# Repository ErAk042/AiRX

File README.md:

# AiRX
AiRX is a modularized fully-analog superheterodyne AM radio receiver for the aviation band (117-140MHz). The system consists of an input filter + LNA, a LNA + mixer stege for converting the band to 7-30MHz range, a Xtal oscillator at 110MHz as the first LO, and a LA1267 based AM radio to demodulate the signal with an additional LM386 amp for driving speakers.

.png)

## Input Stage
The input stage is a 9th order bandpass filter (117-40MHz passband) made using high-q aircore inductors. Right after the filter, there is a LNA block made using the BFP196W RF transistor. Bias network is made using a BC807 PNP transistor. The circuit aims to provide a 15mA current flow over the RF transistor. The overall gain of the LNA block here is around 15dB. The final PCB ins enclosed in a phosphorus-bronze enclosure and the power supply cable is filtered by going through a ferride bead to minimize the RF interference by nearby electronics.

The input stage inside it's enclosure. The sides of the lid are bent frequently with small cuts to improve the seal.

The populated PCB of the input stage. The 3rd SMA connector on the long edge was a temporary test point between the filter and LNA.

## 110MHz Oscillator
A 22MHz crystal is used in 5th overtone to achieve 110MHz 1st LO frequency. There is a filter at the output of the oscillator buffer to filter out any potential harmonics/noise.

## Mixer Stage
The mixer used to bring the band down to the HF range is a SA612 double balanced mixer. At the RF input there is another LNA based on the same BFP196W transistor. It's the same circuit as the input stage LNA, only difference being that the current going through the transistor is roughly 1.4x higher. After that, the signal is fed to the 612's RF input with a 4:1 balun. Since the input impedance of the 612 is around 2kOhms, this balun allows the output of the transistor to be matched better than a straight transmission line. Since the band used is pretty wide, a matching network was not a practical solution in this case.
The 110MHz is directly fed into the base of the internal oscillator transistor of the 612.
At the output, there is a LPF with a cutoff frequency of 30MHz. This both filters out the images and reduces the overall noise level of the system.

The back side of the mixer module.

The front side of the mixer module.

## AM Demodulator
The signals from the mixer module is directly fed to the input of this module. This is a superheterodyne shortwave radio based on the LA1267 chip by Sanyo. At the input, there is a variable band selective filter. The variable capacitor determines the band, as well as the LO frequency of the radio. The audio output is then fed into a LM386 amplifier. The outout can be directly used to drive medium-sized speakers. For the sake of conveniency, I later used a Si5351 frequency sythesizer controlled by an Arduino as the LO to precisely select the band that I wanted to listen to. I was able to account for the slight offset(24KHz) of the 110MHz oscillator with this solution, while achieving precise frequency control. This was a huge improvement since the bandwith is limited to 6-8KHz, which makes it hard to manually adjust the frequency using the variable capacitor without any pulley system. 

The back side of the demodulator module.

The front side of the demodulator module.

## Planned future updates
I'm palnning on using a variable frequency filter for the input stage, which shoould help with the overall sensetivity of the system by limiting the witdh of the band admitted. Also, I want to use a more powerful mixer for the fisr mixer stage, so the dynamic range of the system can be improved. An AGC system is also within my plans.

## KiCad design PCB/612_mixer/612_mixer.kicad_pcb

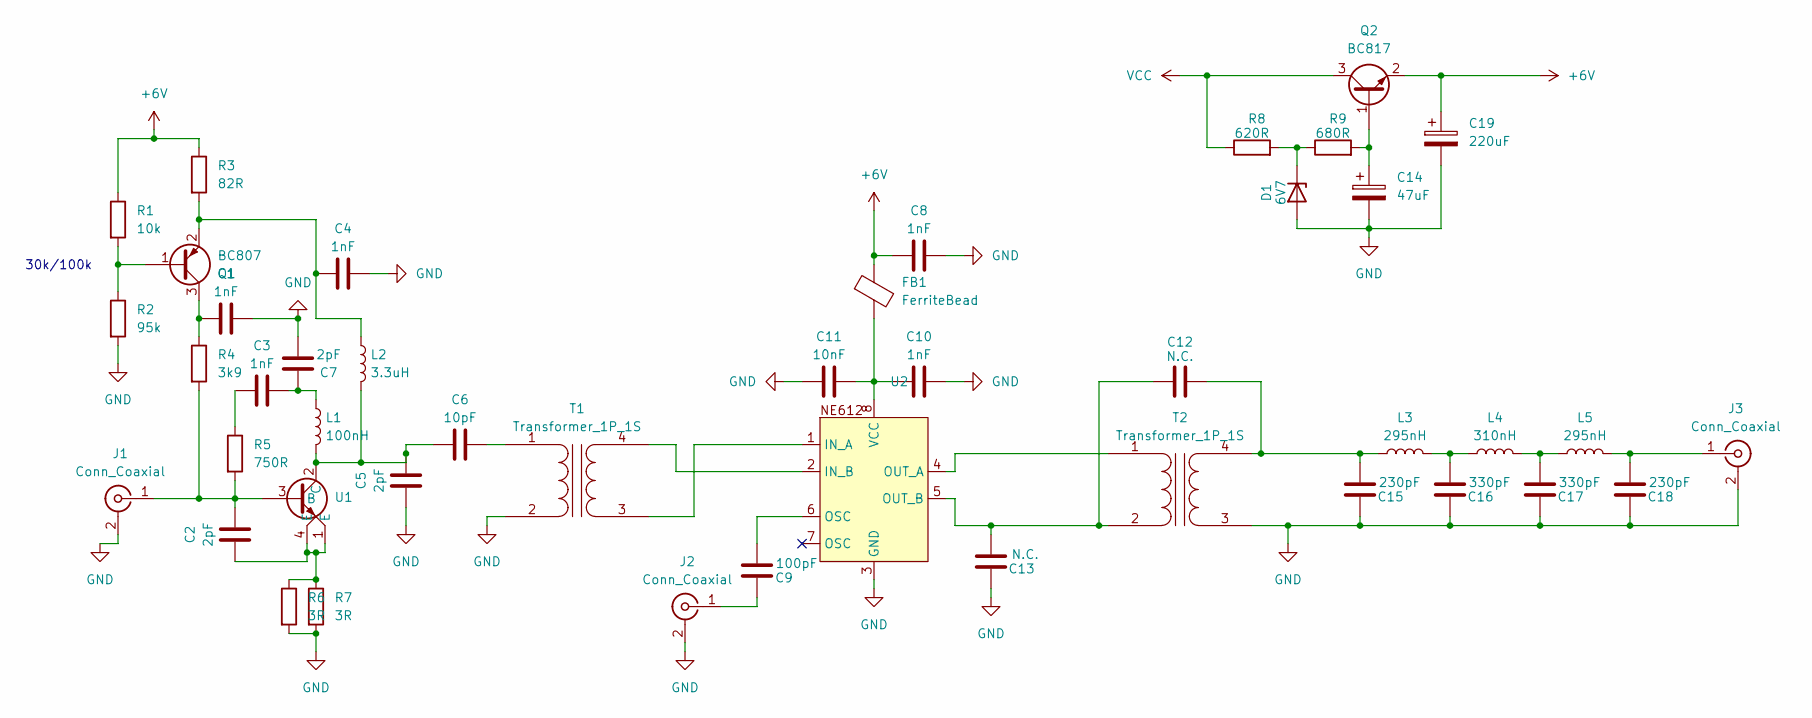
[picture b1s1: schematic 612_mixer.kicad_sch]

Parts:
C1, C3, C4, C8, C10: 1nF; C_0603_1608Metric
C2, C5, C7: 2pF; C_0603_1608Metric
C6: 10pF; C_0603_1608Metric
C9: 100pF; C_0603_1608Metric
C11: 10nF; C_0603_1608Metric
C12, C13: N.C.; C_0603_1608Metric
C14: 47uF; CP_EIA-3528-21_Kemet-B
C15, C18: 230pF; C_0603_1608Metric
C16, C17: 330pF; C_0603_1608Metric
C19: 220uF; CP_EIA-6032-28_Kemet-C
D1: 6V7; L_1206_3216Metric
FB1: FerriteBead; C_0603_1608Metric
J1, J2, J3: Conn_Coaxial; SMA_Samtec_SMA-J-P-H-ST-EM1_EdgeMount
L1: 100nH; L_0402_1005Metric
L2: 3.3uH; L_1008_2520Metric
L3, L5: 295nH; R_Axial_DIN0207_L6.3mm_D2.5mm_P7.62mm_Horizontal
L4: 310nH; R_Axial_DIN0207_L6.3mm_D2.5mm_P7.62mm_Horizontal
Q1: BC807; SOT-323_SC-70
Q2: BC817; SOT-23
R1: 10k; R_0603_1608Metric
R2: 95k; R_0603_1608Metric
R3: 82R; R_0603_1608Metric
R4: 3k9; R_0603_1608Metric
R5: 750R; R_0603_1608Metric
R6, R7: 3R; R_0603_1608Metric
R8: 620R; R_0603_1608Metric
R9: 680R; R_0603_1608Metric
T1, T2: Transformer_1P_1S; SW_DIP_SPSTx02_Slide_6.7x6.64mm_W7.62mm_P2.54mm_LowProfile
U1: SOT343_Transistor
U2: DIP-8_W7.62mm

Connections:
+6V: C8.2, C19.1, FB1.1, Q2.2 (E), R1.1, R3.1
GND: C1.1, C4.1, C5.2, C7.2, C8.1, C10.1, C11.1, C13.1, C14.2, C15.1, C16.1, C17.1, C18.1, C19.2, D1.2 (A), J1.2 (Ext), J2.2 (Ext), J3.2 (Ext), R2.2, R6.2, R7.2, T1.2 (AB), T2.3 (SA), U2.3 (GND)
unnamed: C2.2, R6.1, R7.1, U1.1 (E), U1.4 (E)
unnamed: C3.1, C7.1, L1.1
unnamed: C3.2, R5.1
unnamed: C9.2, U2.6 (OSC)
unnamed: C16.2, L3.2, L4.1
unnamed: C17.2, L4.2, L5.1
unnamed: D1.1 (K), R8.2, R9.1
unnamed: C2.1, J1.1 (In), R4.2, R5.2, U1.3 (B)
unnamed: C9.1, J2.1 (In)
unnamed: C18.2, J3.1 (In), L5.2
unnamed: Q1.1 (B), R1.2, R2.1
unnamed: C1.2, Q1.3 (C), R4.1
unnamed: C4.2, L2.1, Q1.2 (E), R3.2
unnamed: C14.1, Q2.1 (B), R9.2
unnamed: C6.1, T1.1 (AA)
unnamed: T1.3 (SA), U2.1 (IN_A)
unnamed: T1.4 (SB), U2.2 (IN_B)
unnamed: T2.1 (AA), U2.4 (OUT_A)
unnamed: C12.2, C13.2, T2.2 (AB), U2.5 (OUT_B)
unnamed: C12.1, C15.2, L3.1, T2.4 (SB)
unnamed: C5.1, C6.2, L1.2, L2.2, U1.2 (C)
unnamed: C10.2, C11.2, FB1.2, U2.8 (VCC)
VCC: Q2.3 (C), R8.1

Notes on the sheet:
30k/100k

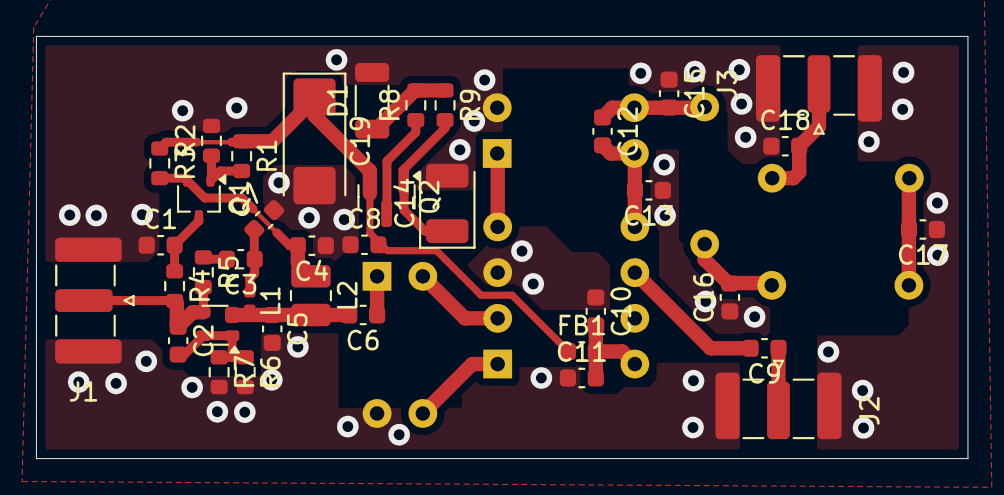
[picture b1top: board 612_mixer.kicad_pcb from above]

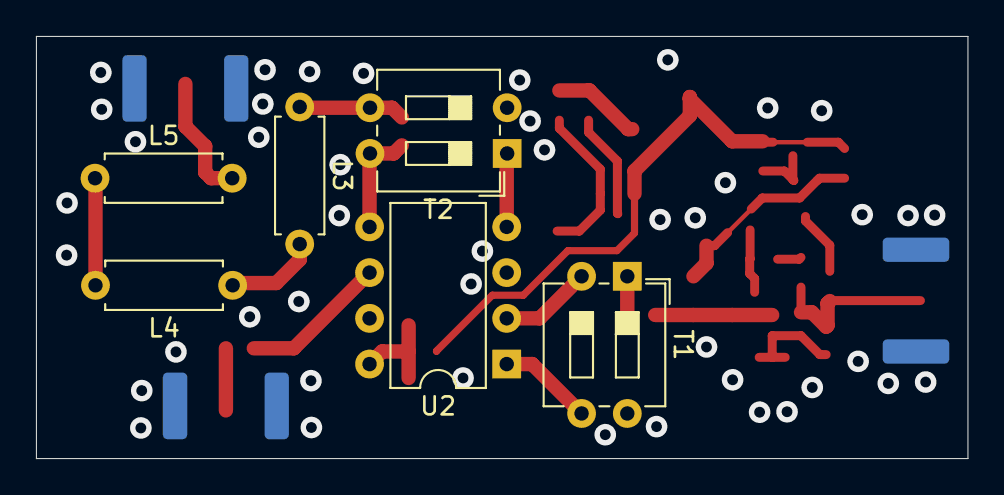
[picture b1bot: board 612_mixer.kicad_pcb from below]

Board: 2 copper layers, 51.8 x 23.5 mm, 44 parts (6 on the bottom side), 25 nets.

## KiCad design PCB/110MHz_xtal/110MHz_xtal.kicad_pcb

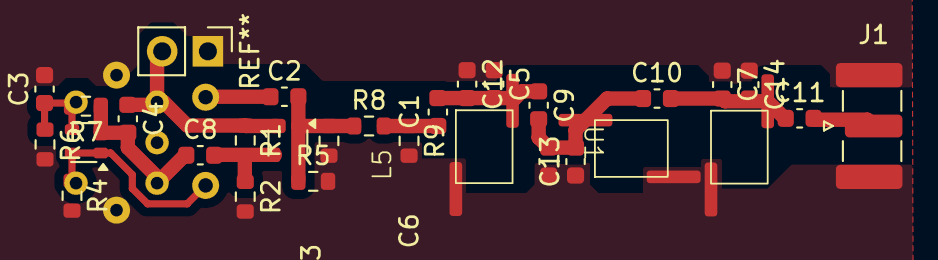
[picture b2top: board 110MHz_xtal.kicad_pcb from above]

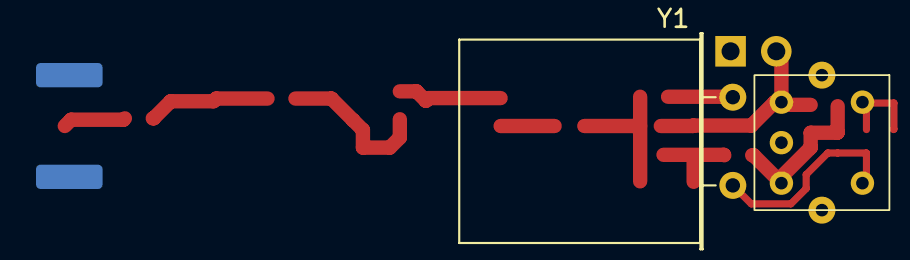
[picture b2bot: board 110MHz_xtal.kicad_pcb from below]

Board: 2 copper layers, 31 parts (2 on the bottom side), 13 nets.

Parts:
C1, C11: 2.9pF; C_0603_1608Metric
C2: 15pF; C_0603_1608Metric
C3, C4, C8: 1nF; C_0603_1608Metric
C5, C12: 17.67pF; C_0603_1608Metric
C6, C13: 20.12pF; C_0603_1608Metric
C7, C14: 17.62pF; C_0603_1608Metric
C9, C10: 0.5pF; C_0603_1608Metric
J1: Conn_Coaxial_Small; SMA_Samtec_SMA-J-P-H-ST-EM1_EdgeMount
L1: Inductor_IF
L4, L5, L6: L; inductor_small
R1: 51k; R_0603_1608Metric
R2, R6: N.C.; R_0603_1608Metric
R3, R8, R9: 15k; R_0603_1608Metric
R4: 330R; R_0603_1608Metric
R5: 150R; R_0603_1608Metric
R7: 470k; R_0603_1608Metric
U1, U2: SOT343_Transistor
Y1: Crystal; Crystal_HC49-U_Horizontal

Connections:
+BATT: C4.1, L1.1, R1.1, U1.2 (C)
GND: C3.2, C5.1, C6.1, C7.1, C12.1, C13.1, C14.1, J1.2 (Ext), L1.6, L4.1, L5.1, L6.1, R2.2, R3.2, R4.2, R5.2, R6.2, R9.2
unnamed: C1.1, R8.2, R9.1
unnamed: C1.2, C5.2, C9.1, C12.2, L4.2
unnamed: C2.1, Y1.1
unnamed: C2.2, R3.1, R5.1, R8.1, U1.1 (E), U1.4 (E)
unnamed: C6.2, C9.2, C10.1, C13.2, L5.2
unnamed: C7.2, C10.2, C11.1, C14.2, L6.2
unnamed: C11.2, J1.1 (In)
unnamed: L1.4, R4.1, U2.1 (E), U2.4 (E), Y1.2
unnamed: C8.2, R1.2, R2.1, U1.3 (B)
unnamed: C3.1, L1.5, R6.1, R7.2, U2.3 (B)
unnamed: C4.2, C8.1, L1.3, R7.1, U2.2 (C)

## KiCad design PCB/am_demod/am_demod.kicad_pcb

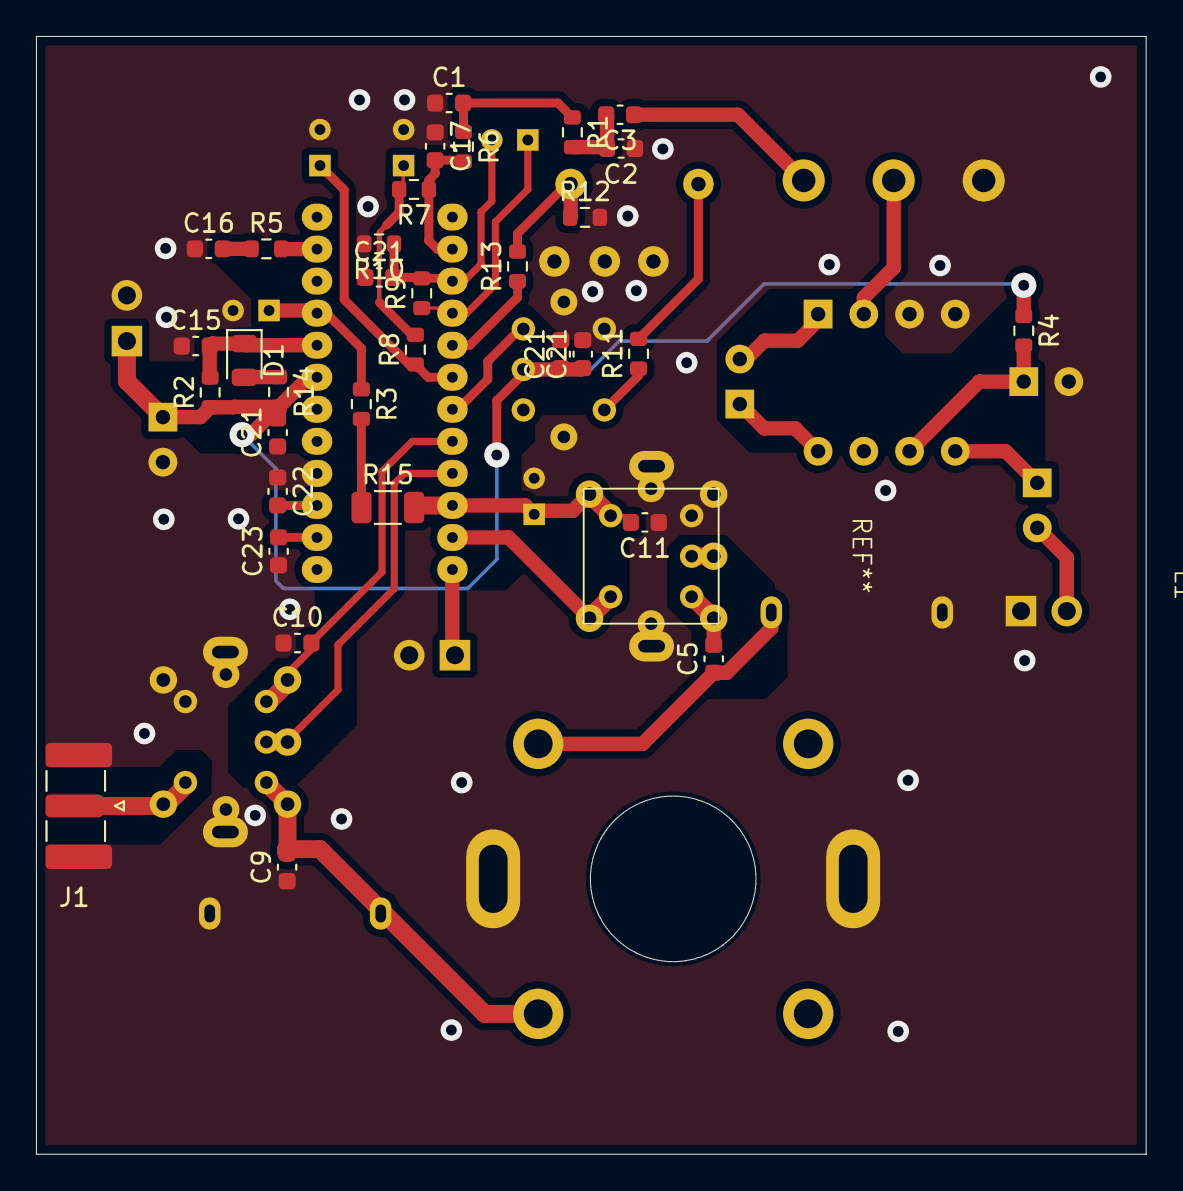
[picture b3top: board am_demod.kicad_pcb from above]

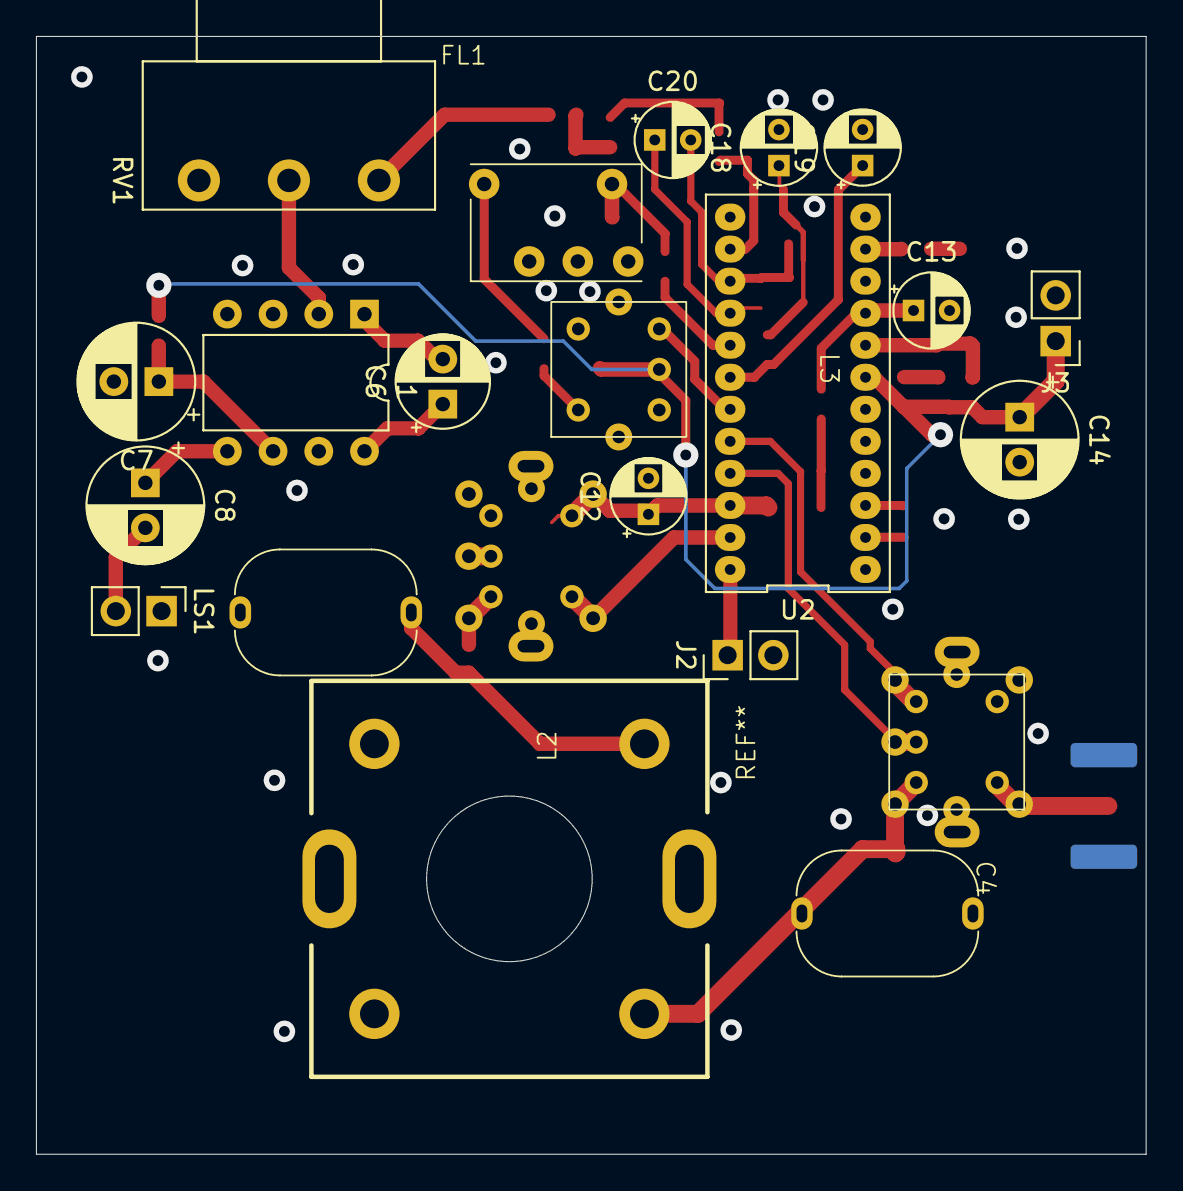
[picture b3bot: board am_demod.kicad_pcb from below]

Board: 2 copper layers, 61.7 x 62.1 mm, 55 parts (22 on the bottom side), 38 nets.

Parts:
C1: 10nF; C_0603_1608Metric
C2: 3.3nF; C_0603_1608Metric
C3: 100nF; C_0603_1608Metric
C4: Variable_Capacitance
C5: 4.7nF; C_0603_1608Metric
C6: 10uF; CP_Radial_D5.0mm_P2.50mm
C7: 100uF; CP_Radial_D6.3mm_P2.50mm
C8: 47uF; CP_Radial_D6.3mm_P2.50mm
C9: 15pF; C_0603_1608Metric
C10, C11, C15, C16, C22, C23: 47n; C_0603_1608Metric
C12, C13, C20: 10µF; CP_Radial_D4.0mm_P2.00mm
C14: 100µF; CP_Radial_D6.3mm_P2.50mm
C17: 15n; C_0603_1608Metric
C18: 3,3µF; CP_Radial_D4.0mm_P2.00mm
C19: 4,7µF; CP_Radial_D4.0mm_P2.00mm
C21, C21#2, C21#3, C21#4: 22nF; C_0603_1608Metric
C24, C25: C_Trim; cap_trim
D1: LED; LED_0805_2012Metric
FL1: A55Ha
J1: Conn_Coaxial; SMA_Samtec_SMA-J-P-H-ST-EM1_EdgeMount
J2, J3: Conn_01x02_Pin; PinHeader_1x02_P2.54mm_Vertical
L1, L2: if_inductor_am
L3: Inductor_IF
LS1: Speaker; PinHeader_1x02_P2.54mm_Vertical
R1: 2K7; R_0603_1608Metric
R2: 1k; R_0603_1608Metric
R3, R5, R14: 15k; R_0603_1608Metric
R4: 10R; R_0603_1608Metric
R6: 3k3; R_0603_1608Metric
R7, R8: 10k; R_0603_1608Metric
R9: 5k1; R_0603_1608Metric
R10: 12k; R_0603_1608Metric
R11, R12, R13: 0R; R_0603_1608Metric
R15: 0R; R_1206_3216Metric
RV1: 10K; Potentiometer_Piher_PC-16_Single_Horizontal
U1: LM386; DIP-8_W7.62mm
U2: DIP-24_296_ELL

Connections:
/AUD: C1.2, R1.1, R6.1
GND: C1.1, C2.1, C4.2, C4.5, C7.2, C9.1, C10.1, C11.1, C12.2, C13.2, C14.2, C15.1, C16.1, C17.1, C18.2, C19.2, C21.2, C21#2.1, C21#3.1, C21#4.2, C22.1, C23.1, C24.1, C25.1, FL1.3, FL1.4 (GND), FL1.5, J1.2 (Ext), J2.2, J3.2, L1.3, L1.6, L1.7, L2.5, L2.6, L2.7, L3.4, L3.6, LS1.1, R10.2, R12.2, RV1.3, U1.3 (+), U1.4 (GND), U2.4 (GND)
unnamed: C2.2, C3.2, R1.2
unnamed: C3.1, RV1.1
unnamed: C5.2, L1.1
unnamed: C6.1, U1.8 (GAIN)
unnamed: C6.2, U1.1 (GAIN)
unnamed: C8.1, U1.5
unnamed: C8.2, LS1.2
unnamed: C10.2, L2.3, U2.20 (AM_IN)
unnamed: C16.2, R5.1
unnamed: C18.1, R7.2, R8.2
unnamed: C20.1, R9.1, U2.16
unnamed: C20.2, C21#3.2, R9.2, R10.1, U2.15
unnamed: C22.2, U2.3
unnamed: C23.2, U2.2
unnamed: C4.4, C9.2, C24.2, L2.1
unnamed: C4.6, C5.1, C25.2
unnamed: D1.2 (A), R14.1
unnamed: C15.2, D1.1 (K), R2.2, U2.8 (LED_IN)
unnamed: FL1.1 (IN), R11.2
unnamed: FL1.2 (OUT), R12.1, R13.2
unnamed: J1.1 (In), L2.4
unnamed: J2.1, U2.24 (OSC_BUF)
unnamed: L2.2, U2.21 (AM_IN)
unnamed: L3.5, R11.1
unnamed: R3.2, R15.1
unnamed: RV1.2, U1.2 (-)
unnamed: C7.1, R4.2, U1.6 (V+)
unnamed: C19.1, R8.1, U2.18 (AGC)
unnamed: R13.1, U2.17 (AIF_IN)
unnamed: L3.3, U2.19 (AMIX_OUT)
unnamed: L1.4, U2.23 (AM_OSC)
unnamed: C17.2, R6.2, R7.1, U2.14 (AM_OUT)
unnamed: C11.2, C12.1, L1.5, R15.2, U2.22 (REG_OUT)
unnamed: C13.1, R3.1, U2.9 (S_CRV)
unnamed: R5.2, U2.11 (S_MET)
VCC: C14.1, C21.1, C21#2.2, C21#4.1, J3.1, L3.2, R2.1, R4.1, R14.2, U2.7 (VCC)

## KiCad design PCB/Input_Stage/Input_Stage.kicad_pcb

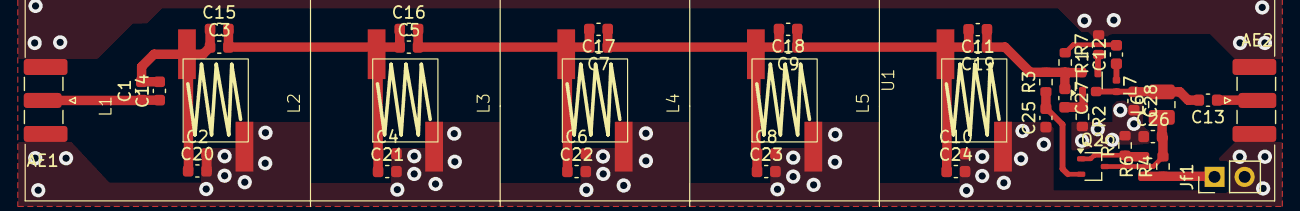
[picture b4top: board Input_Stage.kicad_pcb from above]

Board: 2 copper layers, 47 parts (0 on the bottom side), 17 nets.

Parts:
AE1, AE2: Antenna; SMA_Samtec_SMA-J-P-H-ST-EM1_EdgeMount
C1, C11, C13, C14, C19: 10pF; C_0603_1608Metric
C2, C10, C20, C24: 12pF; C_0603_1608Metric
C3, C9, C15, C18: 2.7pF; C_0603_1608Metric
C4, C6, C8, C21, C22, C23: 15pF; C_0603_1608Metric
C5, C7, C16, C17: 1.8pF; C_0603_1608Metric
C12, C25, C26: 1nF; C_0603_1608Metric
C27, C28: 2pF; C_0603_1608Metric
Jf1: Conn_01x02_Pin; PinHeader_1x02_P2.54mm_Vertical
L1, L2, L3, L4, L5: 3.3uH; Inductor_Aircore
L6: 3.3uH; L_1008_2520Metric
L7: 100nH; L_0402_1005Metric
Q2: BC807; SOT-323_SC-70
R1: 750R; R_0603_1608Metric
R2, R7: 3R; R_0603_1608Metric
R3: 3k9; R_0603_1608Metric
R4: 82R; R_0603_1608Metric
R5: 95k; R_0603_1608Metric
R6: 10k; R_0603_1608Metric
U1: SOT343_Transistor

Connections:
+BATT: Jf1.1, R4.1, R6.1
GND: AE1.2, AE2.2, C2.2, C4.2, C6.2, C8.2, C10.2, C20.2, C21.2, C22.2, C23.2, C24.2, C25.1, C26.1, C28.2, Jf1.2, L1.2, L2.2, L3.2, L4.2, L5.2, R2.2, R5.2, R7.2
unnamed: AE1.1 (A), C1.1, C14.1
unnamed: AE2.1 (A), C13.1
unnamed: C1.2, C2.1, C3.1, C14.2, C15.1, C20.1, L1.1
unnamed: C9.1, C10.1, C11.2, C18.1, C19.2, C24.1, L5.1
unnamed: C12.1, L7.1
unnamed: C12.2, R1.1
unnamed: C3.2, C4.1, C5.1, C15.2, C16.1, C21.1, L2.1
unnamed: C5.2, C6.1, C7.2, C16.2, C17.2, C22.1, L3.1
unnamed: C7.1, C8.1, C9.2, C17.1, C18.2, C23.1, L4.1
unnamed: C27.2, R2.1, R7.1, U1.1 (E), U1.3 (E)
unnamed: Q2.1 (B), R5.1, R6.2
unnamed: C26.2, L6.1, Q2.3 (C), R4.2
unnamed: C25.2, Q2.2 (E), R3.1
unnamed: C11.1, C19.1, C27.1, R1.2, R3.2, U1.4 (B)
unnamed: C13.2, C28.1, L6.2, L7.2, U1.2 (C)

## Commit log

2024-12-23 Create a
